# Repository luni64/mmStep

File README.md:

# mmStep
Stepper driver board compatible to the SparkFun MicroMod system for DRV8825, A4988 etc. driver boards.

## Features:
- Up to 4 stepper driver modules with standard layout (DRV8825, A4988 etc.)
- V<sub>IN</sub> can be chosen from USB (standard) or an external (4-6V) supply
- V<sub>MOT</sub>:  8-35V
- Micro-step selection as well as enable are handled by a I2C multiplexer (MCP23017)
- STEP/DIR signals are directly connected to the GPIOs
- A couple of signals are broken out on pads (100 mil raster) to connect to the outside world (see silk screen on the bottom layer)
- Two layer, 81x49mm
- USB-C connector

## Production data
Here a [link](https://octopart.com/bom-tool/kZcnFrtS) to an Octopart BOM
containing live updated prices and availability from major distributors. It also
provides links to datasheets, and technical information and alternative parts.

Gerbers and drill files can be found in the [production](/Production) folder

Schematic, pictures, pinouts and datasheets can be found in the [documentation](/Documentation) folder.

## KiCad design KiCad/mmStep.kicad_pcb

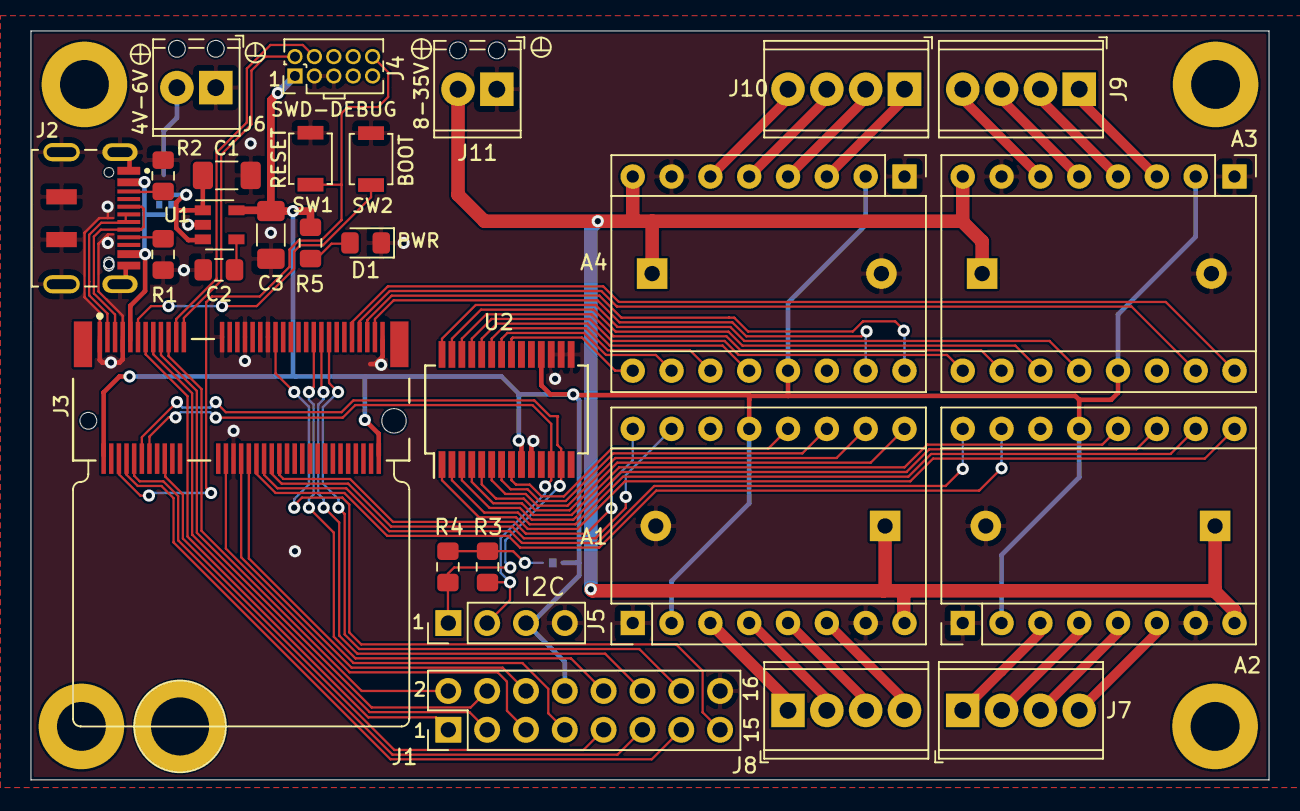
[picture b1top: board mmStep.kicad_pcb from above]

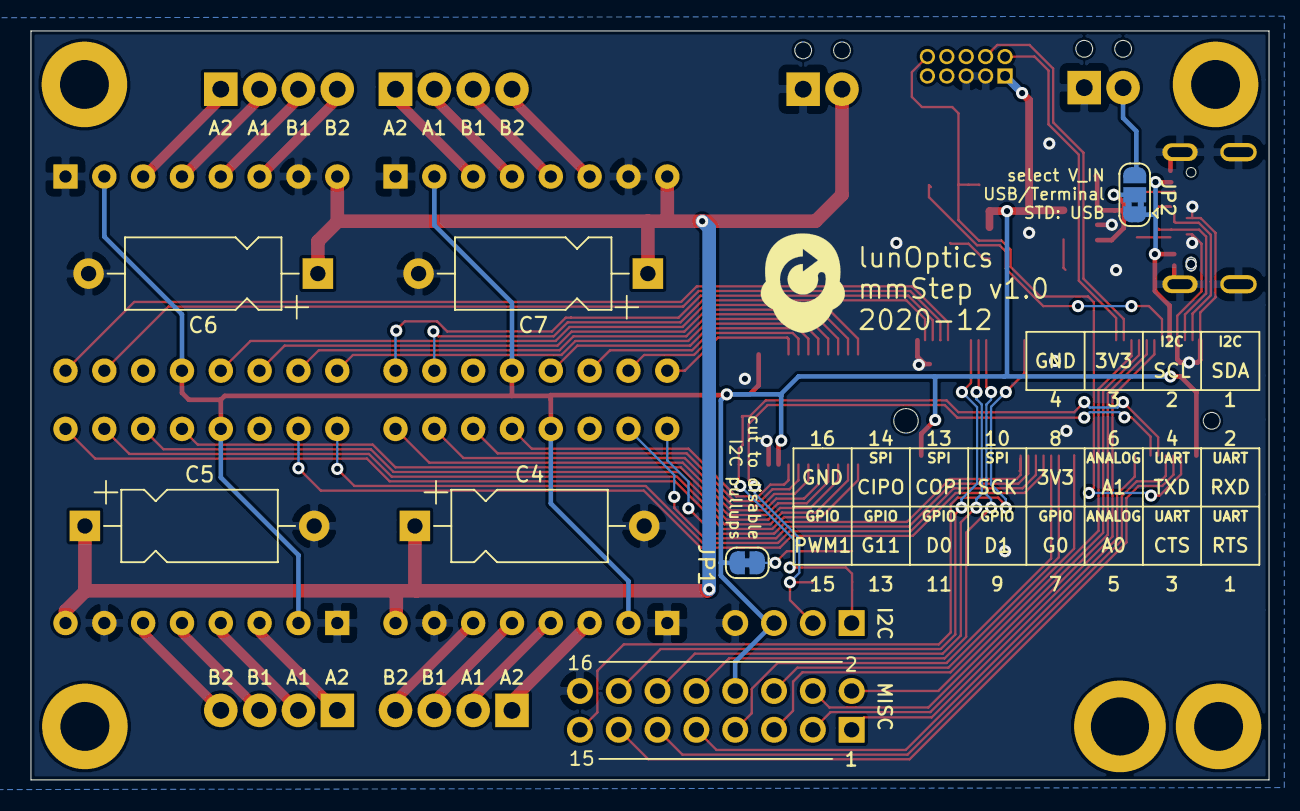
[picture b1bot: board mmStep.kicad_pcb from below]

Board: 2 copper layers, 81.0 x 49.0 mm, 34 parts (6 on the bottom side), 73 nets.

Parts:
A1, A2, A3, A4: Pololu_Breakout_DRV8825; Pololu_Breakout-16_15.2x20.3mm
C1: 1u; C_1206_3216Metric_Pad1.33x1.80mm_HandSolder
C2: 470p; C_0805_2012Metric_Pad1.15x1.40mm_HandSolder
C3: 2u2; C_1206_3216Metric_Pad1.33x1.80mm_HandSolder
C4, C5, C6, C7: 47u; CP_Axial_L10.0mm_D4.5mm_P15.00mm_Horizontal
D1: LED_0805; LED_0805_2012Metric_Pad1.15x1.40mm_HandSolder
J1: Conn_02x08_Top_Bottom; PinHeader_2x08_P2.54mm_Vertical
J2: DX07S016JA1R1500; JAE_DX07S016JA1R1500
J3: MICROMOD-2222-C; TE_Connectivity-2199230-4-Handsolder
J4: Pin Head 50mil; PinHeader_2x05_P1.27mm_Vertical
J5: I2C; PinHeader_1x04_P2.54mm_Vertical
J6, J11: Screw_Term 100mil 1x2; TerminalBlock_Phoenix_MPT-0,5-2-2.54_1x02_P2.54mm_Horizontal
J7, J9: Screw_Terminal_01x04; TerminalBlock_Phoenix_MPT-0,5-4-2.54_1x04_P2.54mm_Horizontal
J8: Screw_Term 100mil 1x4; TerminalBlock_Phoenix_MPT-0,5-4-2.54_1x04_P2.54mm_Horizontal
J10: Screw Term 100mil 1x4; TerminalBlock_Phoenix_MPT-0,5-4-2.54_1x04_P2.54mm_Horizontal
JP1: SolderJumper_2_Bridged; SolderJumper-2_P1.3mm_Bridged_RoundedPad1.0x1.5mm
JP2: SolderJumper_3_Bridged12; SolderJumper-3_P1.3mm_Bridged2Bar12_RoundedPad1.0x1.5mm
R1, R2: 5k1; R_0805_2012Metric_Pad1.15x1.40mm_HandSolder
R3, R4: 2k2; R_0805_2012Metric_Pad1.15x1.40mm_HandSolder
R5: 1k; R_0805_2012Metric_Pad1.15x1.40mm_HandSolder
SW1: B3U1000P; SW_SPST_B3U-1000P
SW2: SW_Push; SW_SPST_B3U-1000P
U1: MIC5219-3.3YM5; SOT-23-5
U2: MCP23017_SS; SSOP-28_5.3x10.2mm_P0.65mm

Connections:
+3V3: A1.2, A1.13, A2.2, A2.13, A3.2, A3.13, A4.2, A4.13, C3.1, J1.8, J3.2, J3.74, J4.1, J5.3, JP1.1, R5.1, U1.5, U2.9, U2.18
/CC1: J2.3, R2.1
/CC2: J2.9, R1.1
/D+: J2.6, J2.7, J3.3
/D-: J2.5, J2.8, J3.5
/Drivers/DIR1: A2.16, J3.44
/Drivers/DIR2: A1.16, J3.48
/Drivers/DIR3: A4.16, J3.71
/Drivers/DIR4: A3.16, J3.67
/Drivers/M01: A1.10, U2.6
/Drivers/M02: A2.10, U2.2
/Drivers/M03: A3.10, U2.26
/Drivers/M04: A4.10, U2.22
/Drivers/M11: A1.11, U2.7
/Drivers/M12: A2.11, U2.3
/Drivers/M13: A3.11, U2.27
/Drivers/M14: A4.11, U2.23
/Drivers/M21: A1.12, U2.8
/Drivers/M22: A2.12, U2.4
/Drivers/M23: A3.12, U2.28
/Drivers/M24: A4.12, U2.24
/Drivers/STP1: A2.15, J3.42
/Drivers/STP2: A1.15, J3.46
/Drivers/STP3: A4.15, J3.73
/Drivers/STP4: A3.15, J3.69
/Drivers/~EN1: A1.9, U2.5
/Drivers/~EN2: A2.9, U2.1
/Drivers/~EN3: A3.9, U2.25
/Drivers/~En4: A4.9, U2.21
/SCL: J3.14, J5.2, R3.1, U2.12
/SDA: J3.12, J5.1, R4.1, U2.13
/SWDCK: J3.21, J4.4
/SWDIO: J3.23, J4.2
/V_IN: J6.2, JP2.3
/V_R: C1.1, JP2.2, U1.1, U1.3
A0: J1.5, J3.34
A1: J1.6, J3.38
BOOT: J3.11, SW2.1
CTS1: J1.3, J3.15
D0: J1.11, J3.10
D1: J1.9, J3.18
G0: J1.7, J3.40
G11: J1.13, J3.8
GND: A1.1, A1.7, A2.1, A2.7, A3.1, A3.7, A4.1, A4.7, C1.2, C2.2, C3.2, C4.2, C5.2, C6.2, C7.2, D1.1, J1.16, J2.1, J2.12, J2.S1, J2.S2, J2.S3, J2.S4, J2.S5, J2.S6, J3.1, J3.7, J3.33, J3.36, J3.39, J3.45, J3.75, J4.3, J4.5, J5.4, J6.1, J11.1, R1.2, R2.2, SW1.2, SW2.2, U1.2, U2.10, U2.15, U2.16, U2.17
unnamed: A1.3, J8.1
unnamed: A1.4, J8.2
unnamed: A1.5, J8.3
unnamed: A1.6, J8.4
unnamed: A2.3, J7.1
unnamed: A2.4, J7.2
unnamed: A2.5, J7.3
unnamed: A2.6, J7.4
unnamed: A3.3, J9.1
unnamed: A3.4, J9.2
unnamed: A3.5, J9.3
unnamed: A3.6, J9.4
unnamed: A4.3, J10.1
unnamed: A4.4, J10.2
unnamed: A4.5, J10.3
unnamed: A4.6, J10.4
unnamed: C2.1, U1.4
unnamed: D1.2, R5.2
unnamed: JP1.2, R3.2, R4.2
PWM1: J1.15, J3.47
RESET: J3.6, J4.10, SW1.1
RTS1: J1.1, J3.13
RX1: J1.2, J3.19
SPI_MISO: J1.14, J3.61
SPI_MOSI: J1.12, J3.59
SPI_SCK: J1.10, J3.57
TX1: J1.4, J3.17
V_USB: J2.2, J2.11, J3.9, JP2.1
Vdrive: A1.8, A2.8, A3.8, A4.8, C4.1, C5.1, C6.1, C7.1, J11.2

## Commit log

2020-12-25 Fixed missing BOOT signal and some ERC errors
2020-12-27 Added Gerbers and drill files
2020-12-27 cleanup
2020-12-27 Updated production data and jlpcb layer jpgs
